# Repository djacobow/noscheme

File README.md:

# NoScheme

NoScheme is a language and compiler for designing PCB circuits using text
rather than drawing schematics.

You can write explicit components and named connections in `.nosch` files,
organize circuits into reusable blocks, and export them to KiCad for placement
and routing. It is designed as a replacement for drawing schematics in
`eeschema`: NoScheme generates the KiCad schematic, one sheet per block, and
KiCad's PCB editor updates the board from it as usual.

The aim is to make circuit descriptions easy to edit, review, and version
alongside firmware, and to provide an extensible set of static checks for
circuits that go beyond traditional ERC rules.

Arrays and reusable component definitions reduce repetition. Electrical rule
checks use declared pin roles and metadata to find connection errors, driver
conflicts, and current, pull-resistance, or capacitance budget violations.

For the time being, the NoScheme compiler and language server are written in
Python. An optional [C++23 implementation](cpp/README.md) shares its compiler
core between the CLI and LSP. Vim, Neovim, Emacs (Eglot), and the local VS Code
extension provide syntax highlighting and LSP integration for diagnostics,
definition navigation, references, rename, hover, completion, and formatting
while editing unsaved designs. `noscheme format` applies the same canonical
layout from the command line.

## History and Rationale

I started my career as a circuit designer in the semiconductor industry,
designing on-chip memories, which is a mixed analog-digital activity. For this
I used schematics, but as tools matured and more work became strictly digital,
I, along with the whole industry, moved largely towards hardware definition
languages such as iHDL (google it), VHDL, and Verilog.

Much later in my career, I found myself designing PCBs, and I was dismayed to
find that the state-of-the-art in PCBA design is still very much schematic
driven. I think this is a shame, because schematics are rather error prone and,
in particular, slow to work on, and hard to add arbitrary checks and
constraints to. Most CAD tools have ERC checks, but to get the full value of
them, you have to annotate nets and pins, which is a tonne of tedious clicking
in a GUI.

While small analog circuits are easy to understand in a visual schematic
format, such circuits comprise a smaller and smaller amount of what goes into
PCB design these days. Instead, we have complex, sprawling nests of digital
wiring and components. You can try to squeeze all those elements onto one
sheet, so you can trace wires, or you can spread them out into many sheets
using tags and named nets, but both ways are very hard for me to trace.

For more than a decade, I had the idea to make a text entry system for PCB
design. Rather than start with a general purpose HDL that supports simulation,
sophisticated generators, and other fancy features, I wanted a domain-specific
language (DSL) that is tightly bound to the target: PCBs. That's NoScheme.

I don't expect to convert many experienced PCB people to this way of working,
but I intend to use NoScheme personally for as many projects as I can manage,
and will extend it as required when I run into limitations. Because of that,
the language should be considered very much experimental, at least for the time
being.

## Status

This is an actively developed proof of concept. Several examples, including an
STM32 reference board, compile, and their netlists have successfully populated a
KiCad board. Every example's generated KiCad schematic reads back in KiCad with
the same connectivity and passes KiCad's schematic ERC. Placement, routing, and hardware validation remain separate steps.

## Documentation

- [Usage guide](USAGE.md) — install the tool, develop a circuit, check it,
  export a BOM, and carry changes into KiCad.
- [Language reference](docs/LRM.md) — normative syntax, scope, metadata, electrical rules,
  and a complete example.
- [Development](docs/DEVELOPMENT.md) — compiler development, tests, CI, and performance measurements.
- [Editor support](docs/EDITOR_SUPPORT.md) — Vim, Neovim, Emacs, and VS Code setup and LSP capabilities.
- [Project design](docs/PROJECT.md) — goals, design decisions, and reference-board details.
- [Implementation history](docs/PLAN.md) — milestone records and deferred proposals.
- [KiCad experiments](docs/experiments/README.md) and
  [findings](docs/experiments/FINDINGS.md) — manual import/update checks and results.

Runnable designs are in [examples/](examples/), including the [STM32
board](examples/stm32h523/stm32h523.nosch) and the [Rulos six-line display
matrix](examples/rulos_6matrix/README.md), transcribed from an existing
schematic using nested block and component arrays. The [WREN
examples](examples/wren/README.md) include a readable 189-component output
subsystem and a generated 1,507-component compiler/LSP benchmark. The [Honest
Millisecond Clock](examples/clock/README.md) is a new GPS-disciplined NTP clock
design with parts selected for JLCPCB assembly.

## License

NoScheme is free software, licensed under the [GNU General Public License v3.0
or later](LICENSE.md). Designs you write in NoScheme and the files it generates
from them are your own; the GPL does not apply to them.

The KiCad library snapshots under `examples/*/kicad_lib/` are derived from the
KiCad libraries and keep their CC-BY-SA 4.0 license; see the `LICENSE.md` in
each of those directories.

The [Rulos](examples/rulos_6matrix/README.md#attribution-and-sources) and
[WREN](examples/wren/README.md#attribution-and-provenance) examples also record
their upstream design attribution and source-license information.

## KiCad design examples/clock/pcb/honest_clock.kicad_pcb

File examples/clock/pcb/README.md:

# Honest Clock PCB

KiCad 10 project for the clock board. It starts empty except for the
outline, mounting holes, planes, and rules; parts arrive from the NoScheme
netlist.

## Board

- **Outline:** 226 × 64 mm, from the layout mockup. Displays face the front;
  everything else mounts on the back.
- **Stand band:** the bottom 9.525 mm (3/8 in) is a rule area named
  `stand band`. `honest_clock.kicad_dru` rejects any footprint there except
  the mounting holes, on either side.
- **Mounting holes:** five M3 holes (H1–H5): two along the top, three in the
  stand band to screw the board to its base. They are board-only footprints,
  so netlist updates keep them.
- **Origins:** the grid origin is the top-left corner; the drill/place origin
  is the bottom-left corner, for JLCPCB position files.

## Stackup

JLCPCB JLC04161H-7628: 4 layers, 1.6 mm, 1 oz outer and 0.5 oz inner copper.

| Layer | Use | Thickness |
|---|---|---|
| F.Cu | Digits (through-hole), front routing | 35 µm |
| Prepreg 7628 | εr 4.4 | 0.2104 mm |
| In1.Cu | Power: 3V3 left of x = 88 mm, 5V right | 15.2 µm |
| Core | εr 4.6 | 1.065 mm |
| In2.Cu | GND plane | 15.2 µm |
| Prepreg 7628 | εr 4.4 | 0.2104 mm |
| B.Cu | Components and most routing | 35 µm |

- **GND on In2:** the ground plane is the layer next to B.Cu, where the parts
  and fast signals are (USB, RMII, the GPS RF trace). That gives them a return
  path 0.21 mm away.
- **In1 split:** 5V feeds the LED supply, about 0.75 A spread across the
  digits on the right, so it gets the plane there. 3V3 serves the MCU, PHY,
  and GPS on the left, where most of the 3V3 pins and decoupling vias are.
  The drivers' 3V3 logic supply is a few milliamps and can run on traces.
- **Split position:** move the split once placement settles. Keep fast
  signals from crossing it on B.Cu: In2 is their reference, so that is mostly
  a concern for routing on F.Cu.

## Rules (6/6/6)

| Rule | Value |
|---|---|
| Track width, minimum | 0.1524 mm (6 mil) |
| Clearance, minimum | 0.1524 mm (6 mil) |
| Via annular ring, minimum | 0.15 mm (~6 mil) |
| Via | 0.6 mm pad on a 0.3 mm drill (also 0.8 / 0.4 preset) |
| Through-hole drill, minimum | 0.3 mm |
| Hole to hole | 0.5 mm |
| Hole to copper | 0.254 mm |
| Copper to board edge | 0.3 mm |
| Silkscreen text | 1.0 mm high, 0.15 mm stroke |

Net classes:

| Class | Track | Clearance | Via | Members |
|---|---|---|---|---|
| Default | 0.1524 mm (6 mil) | 0.1524 mm | 0.6 / 0.3 | everything else |
| Power | 0.2032 mm (8 mil) | 0.1524 mm | 0.6 / 0.3 | `vbus`, `v5`, `v3v3`, `v3v3_quiet`, `gnd` |

8 mil is a minimum for rails, not a target. Use the planes, or widen tracks
where current flows: VBUS at 12 V, the buck switch nodes and outputs, and the
LED 5 V supply.

## Project footprints

`HonestClock.pretty` holds footprints drawn for this board, registered in the
project's `fp-lib-table` as `HonestClock`:

- **`OLED_SSD1309_2.42in_Module`:** the whole 2.42" OLED module, not just its
  header: the 72 × 43 mm outline on silkscreen and courtyard, the glass and
  active area on F.Fab, the 7-pin header (origin at pin 1, GND), and four
  2.2 mm holes for M2 screws on the module's 68 × 39 mm pattern. Dimensions
  follow QDtech's MC242GX drawing; measure a real module before ordering.
- **`RJ45_HanRun_HY951180A_Vertical`:** the vertical MagJack, from HanRun's
  recommended PCB layout: eight signal pins, four LED pins, two shield tabs,
  and two 3.2 mm locating pegs. Origin at pin 1.

- **`USB_C_Receptacle_Hanxia_HX-TYPE-C-16P-180-LT-H10.0_Vertical`:** the
  vertical USB-C receptacle, from Hanxia's recommended layout: two rows of
  eight SMD pads at 1.00 mm, four SMD shell tabs, and two 0.9 mm peg holes.
  The shell tabs are 0.12 mm shorter than drawn to keep 0.25 mm from the peg
  holes.

`scripts/make_footprints.py` regenerates them from named dimensions.

After changing a footprint here, refresh its record in
`kicad_lib/footprints.json` (see [kicad_lib/README.md](../kicad_lib/README.md)).

## Scripts

`snapshots/` (local, not committed) holds a copy of the board at each
placement step, numbered in order.

Run these from KiCad's scripting console with the board open, or standalone
on a closed board (`python3 scripts/<name>.py honest_clock.kicad_pcb`):

- **`place_clusters.py`:** places the subsystems (USB/PD, bucks, GPS,
  Ethernet, timebase, MCU passives, probes) as clusters: each anchor part at
  a target spot, then its decoupling caps on its power pins and its other
  passives beside the pins or parts they connect to. Parts in `KEEP` stay
  where they were placed by hand. Edit `CLUSTERS` and rerun from a snapshot.
  With `--only REF ...` it re-places just those satellites around their
  anchors' current positions and leaves every other part where it is, which
  suits tidying up after moving parts by hand. Add `--here` to nudge named
  anchors to the nearest free spot around their current positions instead.
- **`place_display_passives.py`:** puts each digit's R-EXT below its bottom
  pin row and its driver's decoupling cap above the driver, both on the back.

## Bring parts in

From the repository root:

```sh
uv run --locked noscheme export-kicad --project examples/clock \
  --footprints examples/clock/kicad_lib/footprints.json \
  --schematic examples/clock/pcb/honest_clock.kicad_sch
```

This writes the KiCad schematic here: `honest_clock.kicad_sch` and one sheet
file per distinct block (the nine digits share `display_Digit.kicad_sch`),
plus `noscheme.kicad_sym`, registered in `sym-lib-table`. They are generated
and committed with the board; edits made in KiCad are overwritten.

1. In KiCad, open `honest_clock.kicad_pro`, then the PCB editor.
2. **Tools → Update PCB from Schematic** (F8). Review the changes, then
   **Update PCB**. The schematic editor need not be open.
3. The plane zones are already tied to `gnd`, `v3v3`, and `v5`; refill zones
   (**B**) once parts are placed.

The board was first populated from `build/board.net`, whose footprint links
differ from the schematic's. The first F8 after that needs **Re-link footprints
to schematic symbols based on their reference designators** ticked.

Net-class membership comes from `net_class: "Power"` in `main.nosch`. The
schematic carries it to the board on every update; the `Power` class's widths
and clearances stay in `honest_clock.kicad_pro`.

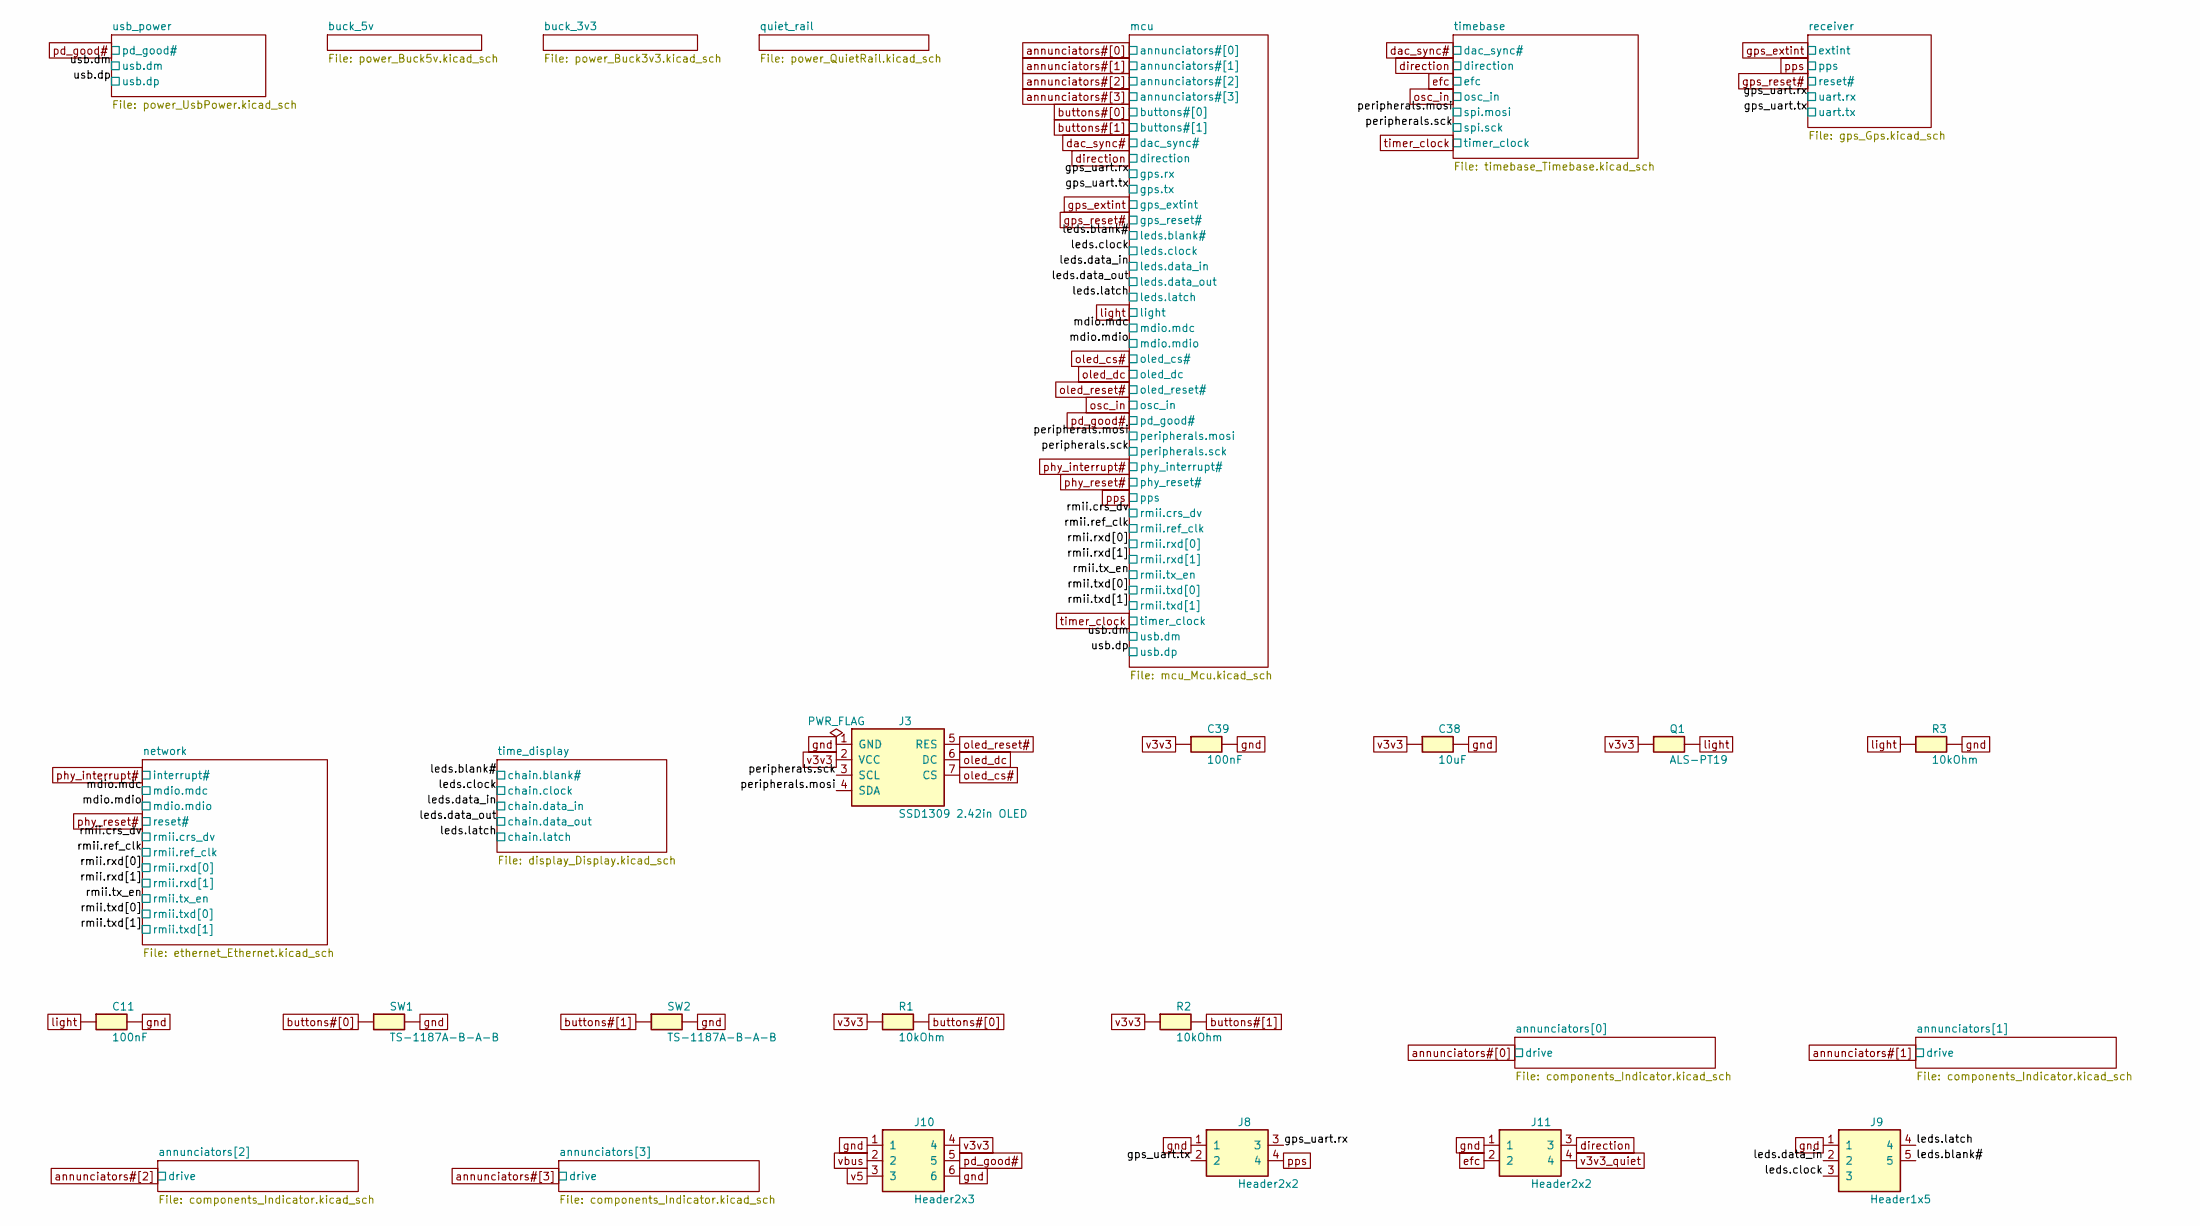
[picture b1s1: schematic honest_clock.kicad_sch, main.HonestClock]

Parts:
C11, C39: 100nF; C_0603_1608Metric
C38: 10uF; C_0805_2012Metric
J3: SSD1309 2.42in OLED; OLED_SSD1309_2.42in_Module
J8, J11: Header2x2; PinHeader_2x02_P2.54mm_Vertical_SMD
J9: Header1x5; PinHeader_1x05_P2.54mm_Vertical_SMD_Pin1Left
J10: Header2x3; PinHeader_2x03_P2.54mm_Vertical_SMD
Q1: ALS-PT19; LED_0603_1608Metric; MPN ALS-PT19-315C/L177/TR8
R1, R2, R3: 10kOhm; R_0603_1608Metric
SW1, SW2: TS-1187A-B-A-B; SW_SPST_TL3342; MPN TS-1187A-B-A-B

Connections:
/gps_uart.rx: J8.3; also elsewhere on the board
/gps_uart.tx: J8.2; also elsewhere on the board
/leds.blank#: J9.5; also elsewhere on the board
/leds.clock: J9.3; also elsewhere on the board
/leds.data_in: J9.2; also elsewhere on the board
/leds.latch: J9.4; also elsewhere on the board
/peripherals.mosi: J3.4 (SDA); also elsewhere on the board
/peripherals.sck: J3.3 (SCL); also elsewhere on the board
buttons#[0]: R1.2, SW1.1; also elsewhere on the board
buttons#[1]: R2.2, SW2.1; also elsewhere on the board
direction: J11.3; also elsewhere on the board
efc: J11.2; also elsewhere on the board
gnd: C11.2, C38.2, C39.2, J3.1 (GND), J8.1, J9.1, J10.1, J10.6, J11.1, R3.2, SW1.2, SW2.2; also elsewhere on the board
light: C11.1, Q1.2 (emitter), R3.1; also elsewhere on the board
oled_cs#: J3.7 (CS); also elsewhere on the board
oled_dc: J3.6 (DC); also elsewhere on the board
oled_reset#: J3.5 (RES); also elsewhere on the board
pd_good#: J10.5; also elsewhere on the board
pps: J8.4; also elsewhere on the board
v3v3: C38.1, C39.1, J3.2 (VCC), J10.4, Q1.1 (collector), R1.1, R2.1; also elsewhere on the board
v3v3_quiet: J11.4; also elsewhere on the board
v5: J10.3; also elsewhere on the board
vbus: J10.2; also elsewhere on the board

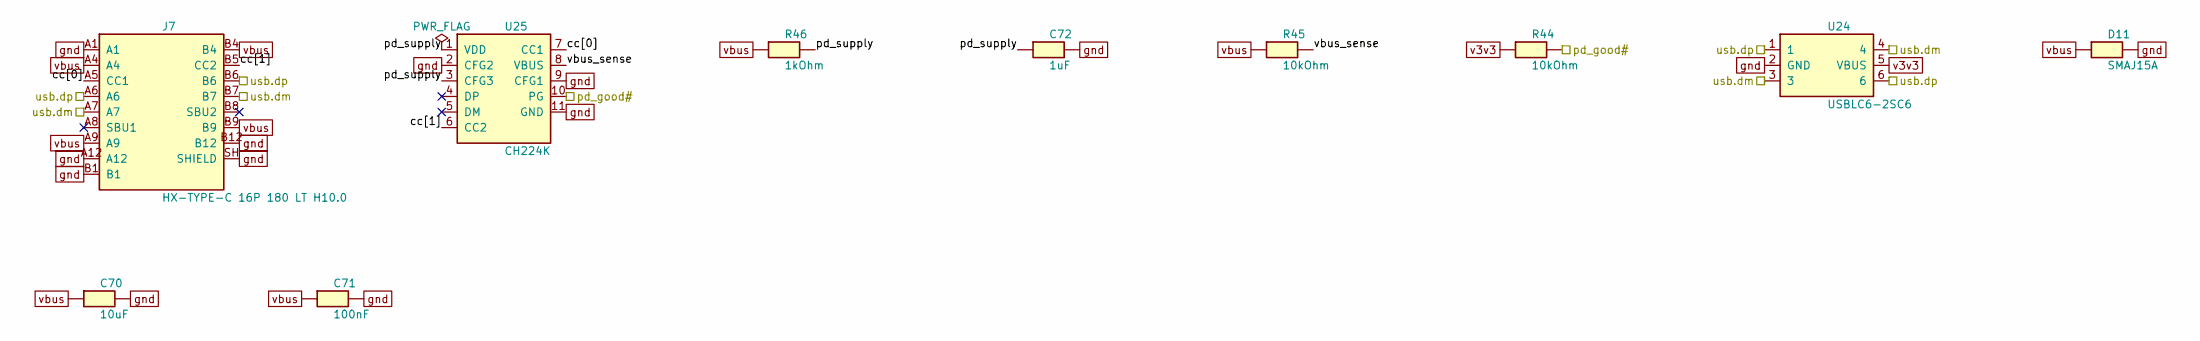
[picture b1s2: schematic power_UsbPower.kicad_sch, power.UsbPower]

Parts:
C70: 10uF; C_1206_3216Metric
C71: 100nF; C_0603_1608Metric
C72: 1uF; C_0603_1608Metric
D11: SMAJ15A; D_SMA; MPN SMAJ15A
J7: HX-TYPE-C 16P 180 LT H10.0; USB_C_Receptacle_Hanxia_HX-TYPE-C-16P-180-LT-H10.0_Vertical; MPN HX-TYPE-C 16P 180 LT H10.0
R44, R45: 10kOhm; R_0603_1608Metric
R46: 1kOhm; R_0603_1608Metric
U24: USBLC6-2SC6; SOT-23-6; MPN USBLC6-2SC6
U25: CH224K; SSOP-10-1EP_3.9x4.9mm_P1mm_EP2.1x3.3mm; MPN CH224K

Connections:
/usb.dm: J7.A7, J7.B7, U24.3, U24.4; also elsewhere on the board
/usb.dp: J7.A6, J7.B6, U24.1, U24.6; also elsewhere on the board
/usb_power/cc[0]: J7.A5 (CC1), U25.7 (CC1)
/usb_power/cc[1]: J7.B5 (CC2), U25.6 (CC2)
/usb_power/pd_supply: C72.1, R46.2, U25.1 (VDD), U25.3 (CFG3)
/usb_power/vbus_sense: R45.2, U25.8 (VBUS)
gnd: C70.2, C71.2, C72.2, D11.2 (anode), J7.A1, J7.A12, J7.B1, J7.B12, J7.SH (SHIELD), U24.2 (GND), U25.2 (CFG2), U25.9 (CFG1), U25.11 (GND); also elsewhere on the board
pd_good#: R44.2, U25.10 (PG); also elsewhere on the board
v3v3: R44.1, U24.5 (VBUS); also elsewhere on the board
vbus: C70.1, C71.1, D11.1 (cathode), J7.A4, J7.A9, J7.B4, J7.B9, R45.1, R46.1; also elsewhere on the board

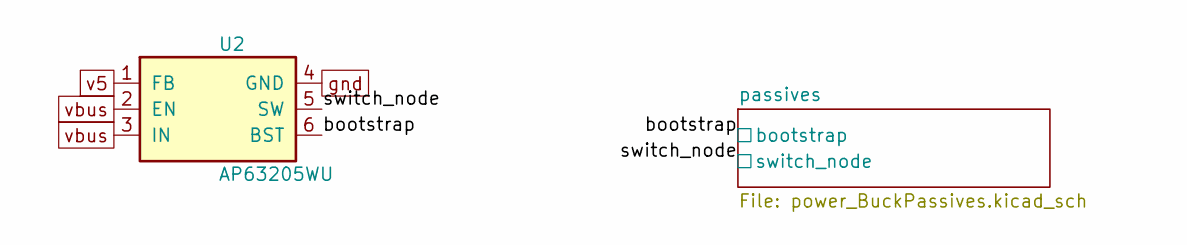
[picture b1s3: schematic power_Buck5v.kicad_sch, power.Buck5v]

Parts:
U2: AP63205WU; TSOT-23-6; MPN AP63205WU-7

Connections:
/buck_5v/bootstrap: U2.6 (BST); also elsewhere on the board
/buck_5v/switch_node: U2.5 (SW); also elsewhere on the board
gnd: U2.4 (GND); also elsewhere on the board
v5: U2.1 (FB); also elsewhere on the board
vbus: U2.2 (EN), U2.3 (IN); also elsewhere on the board

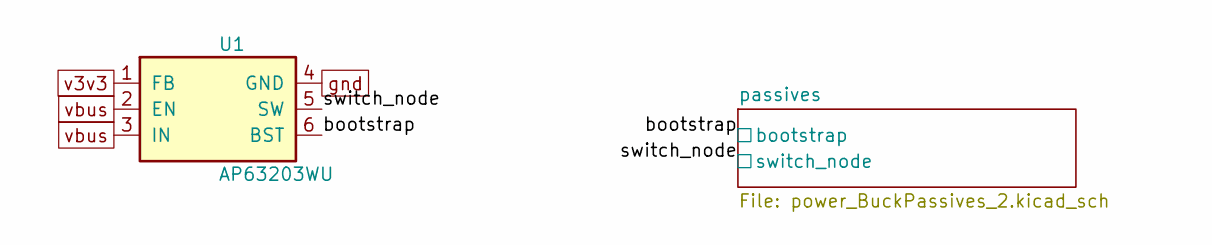
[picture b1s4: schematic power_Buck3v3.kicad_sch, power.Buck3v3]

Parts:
U1: AP63203WU; TSOT-23-6; MPN AP63203WU-7

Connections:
/buck_3v3/bootstrap: U1.6 (BST); also elsewhere on the board
/buck_3v3/switch_node: U1.5 (SW); also elsewhere on the board
gnd: U1.4 (GND); also elsewhere on the board
v3v3: U1.1 (FB); also elsewhere on the board
vbus: U1.2 (EN), U1.3 (IN); also elsewhere on the board

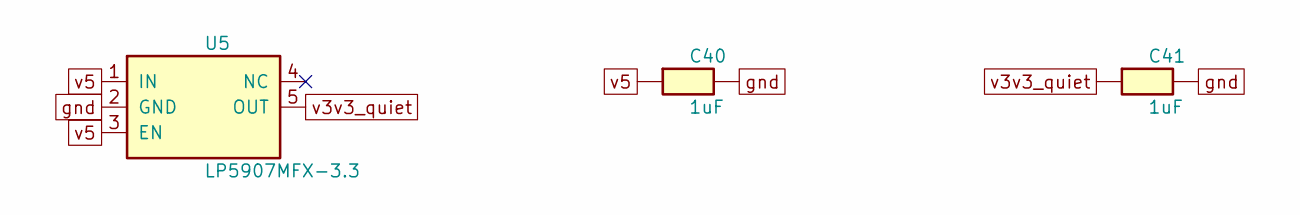
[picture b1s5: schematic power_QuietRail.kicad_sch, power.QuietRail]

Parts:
C40, C41: 1uF; C_0603_1608Metric
U5: LP5907MFX-3.3; SOT-23-5; MPN LP5907MFX-3.3/NOPB

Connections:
gnd: C40.2, C41.2, U5.2 (GND); also elsewhere on the board
v3v3_quiet: C41.1, U5.5 (OUT); also elsewhere on the board
v5: C40.1, U5.1 (IN), U5.3 (EN); also elsewhere on the board

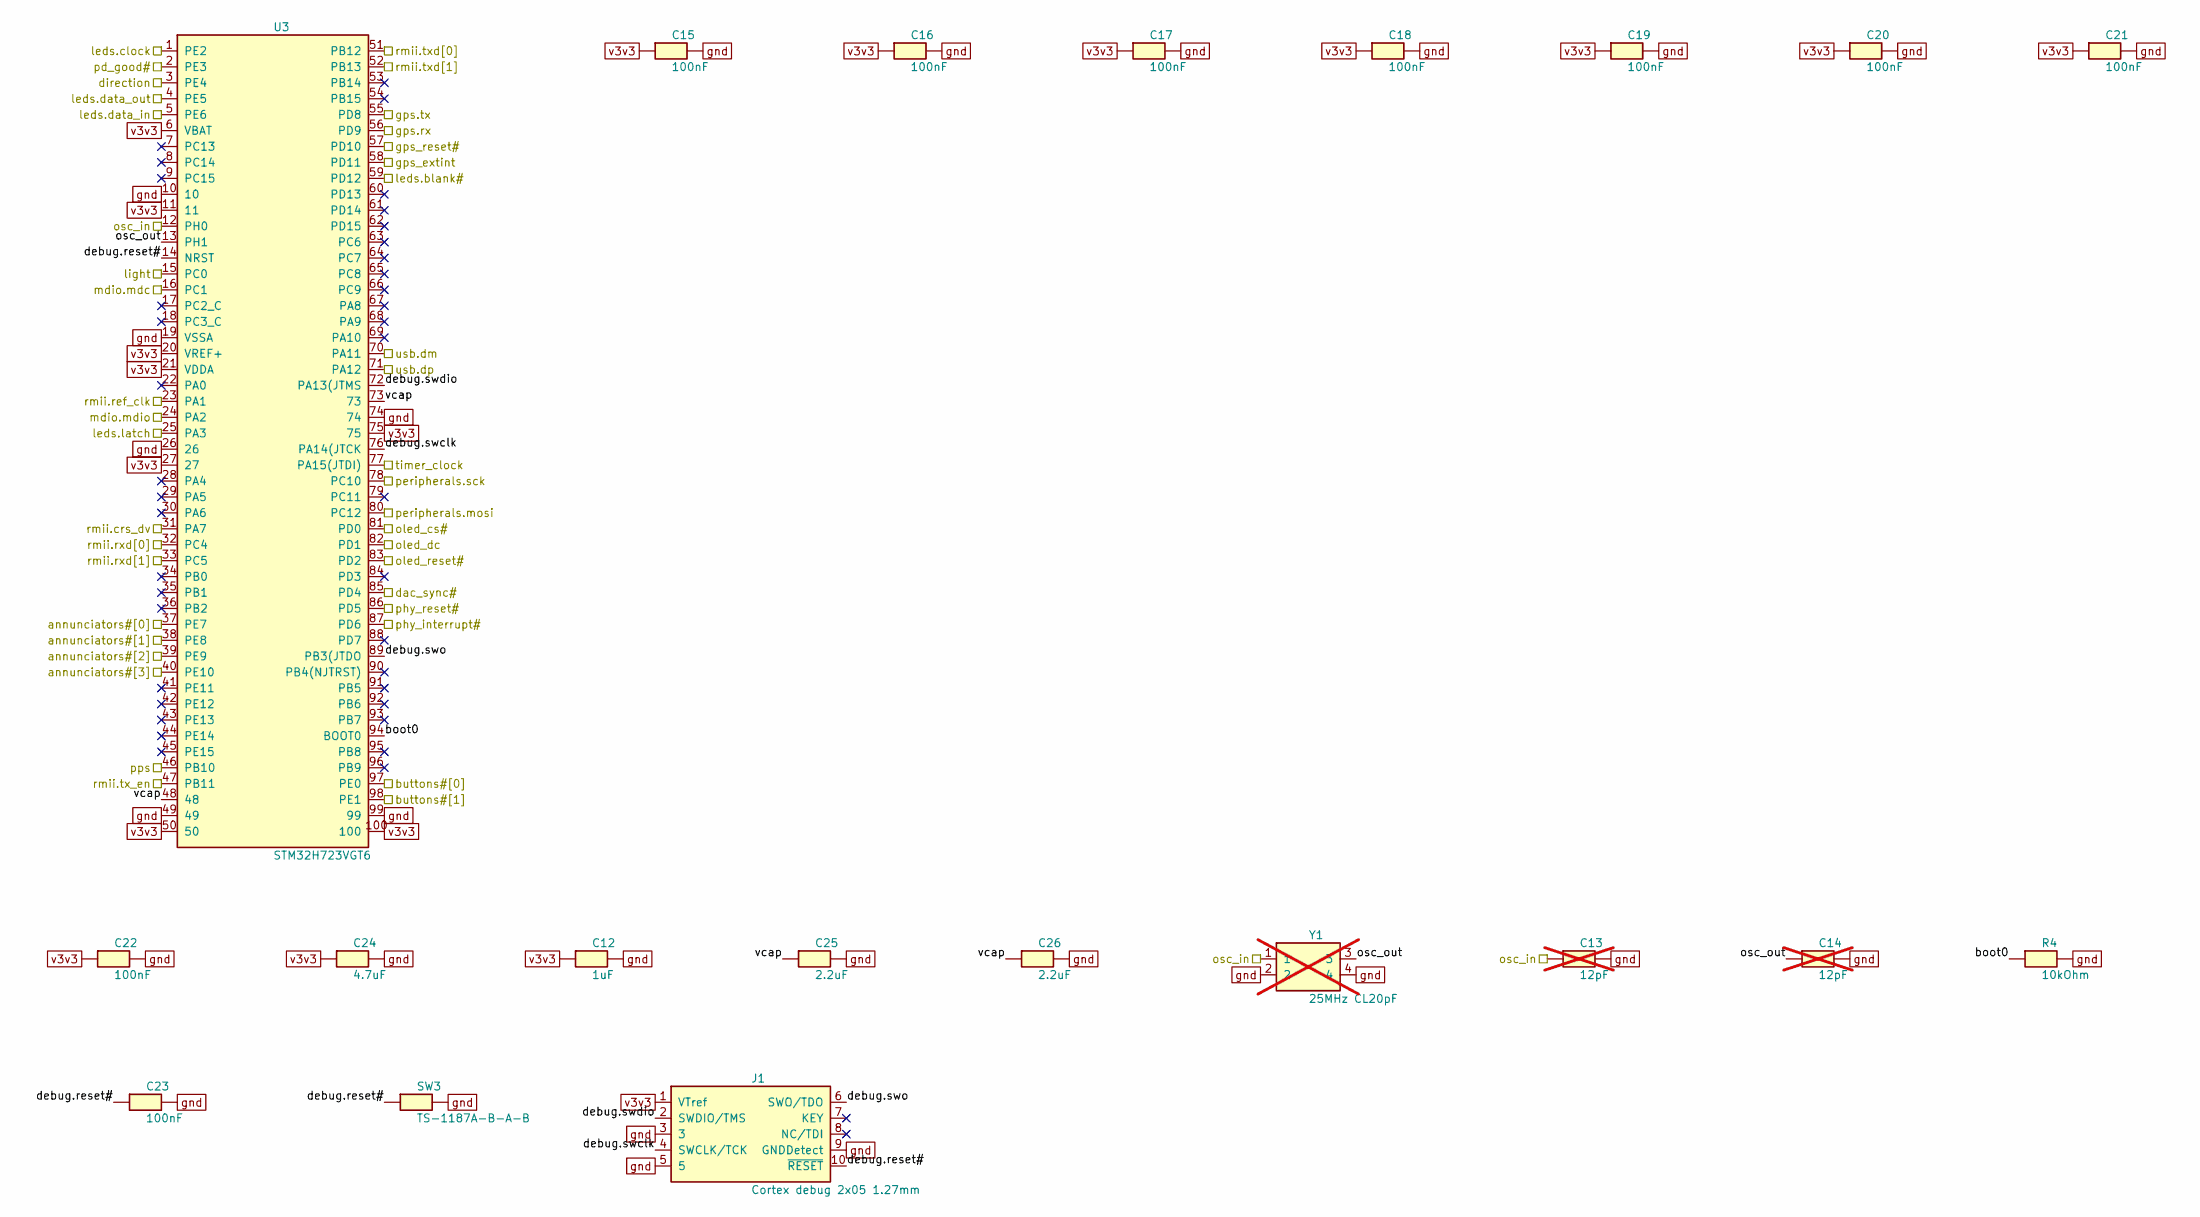
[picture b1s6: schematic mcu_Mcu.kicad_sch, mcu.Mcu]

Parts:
C12: 1uF; C_0603_1608Metric
C13, C14: 12pF; C_0603_1608Metric; not fitted
C15, C16, C17, C18, C19, C20, C21, C22, C23: 100nF; C_0603_1608Metric
C24: 4.7uF; C_0603_1608Metric
C25, C26: 2.2uF; C_0603_1608Metric
J1: Cortex debug 2x05 1.27mm; PinHeader_2x05_P1.27mm_Vertical_SMD
R4: 10kOhm; R_0603_1608Metric
SW3: TS-1187A-B-A-B; SW_SPST_TL3342; MPN TS-1187A-B-A-B
U3: STM32H723VGT6; LQFP-100_14x14mm_P0.5mm; MPN STM32H723VGT6
Y1: 25MHz CL20pF; Crystal_SMD_3225-4Pin_3.2x2.5mm; MPN X322525MOB4SI; not fitted

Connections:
/gps_uart.rx: U3.56 (PD9); also elsewhere on the board
/gps_uart.tx: U3.55 (PD8); also elsewhere on the board
/leds.blank#: U3.59 (PD12); also elsewhere on the board
/leds.clock: U3.1 (PE2); also elsewhere on the board
/leds.data_in: U3.5 (PE6); also elsewhere on the board
/leds.data_out: U3.4 (PE5); also elsewhere on the board
/leds.latch: U3.25 (PA3); also elsewhere on the board
/mcu/boot0: R4.1, U3.94 (BOOT0)
/mcu/debug.reset#: C23.1, J1.10 (~RESET), SW3.1, U3.14 (NRST)
/mcu/debug.swclk: J1.4 (SWCLK/TCK), U3.76 (PA14(JTCK)
/mcu/debug.swdio: J1.2 (SWDIO/TMS), U3.72 (PA13(JTMS)
/mcu/debug.swo: J1.6 (SWO/TDO), U3.89 (PB3(JTDO)
/mcu/osc_out: C14.1, U3.13 (PH1), Y1.3
/mcu/vcap: C25.1, C26.1, U3.48, U3.73
/mdio.mdc: U3.16 (PC1); also elsewhere on the board
/mdio.mdio: U3.24 (PA2); also elsewhere on the board
/peripherals.mosi: U3.80 (PC12); also elsewhere on the board
/peripherals.sck: U3.78 (PC10); also elsewhere on the board
/rmii.crs_dv: U3.31 (PA7); also elsewhere on the board
/rmii.ref_clk: U3.23 (PA1); also elsewhere on the board
/rmii.rxd[0]: U3.32 (PC4); also elsewhere on the board
/rmii.rxd[1]: U3.33 (PC5); also elsewhere on the board
/rmii.tx_en: U3.47 (PB11); also elsewhere on the board
/rmii.txd[0]: U3.51 (PB12); also elsewhere on the board
/rmii.txd[1]: U3.52 (PB13); also elsewhere on the board
/usb.dm: U3.70 (PA11); also elsewhere on the board
/usb.dp: U3.71 (PA12); also elsewhere on the board
annunciators#[0]: U3.37 (PE7); also elsewhere on the board
annunciators#[1]: U3.38 (PE8); also elsewhere on the board
annunciators#[2]: U3.39 (PE9); also elsewhere on the board
annunciators#[3]: U3.40 (PE10); also elsewhere on the board
buttons#[0]: U3.97 (PE0); also elsewhere on the board
buttons#[1]: U3.98 (PE1); also elsewhere on the board
dac_sync#: U3.85 (PD4); also elsewhere on the board
direction: U3.3 (PE4); also elsewhere on the board
gnd: C12.2, C13.2, C14.2, C15.2, C16.2, C17.2, C18.2, C19.2, C20.2, C21.2, C22.2, C23.2, C24.2, C25.2, C26.2, J1.3, J1.5, J1.9 (GNDDetect), R4.2, SW3.2, U3.10, U3.19 (VSSA), U3.26, U3.49, U3.74, U3.99, Y1.2, Y1.4; also elsewhere on the board
gps_extint: U3.58 (PD11); also elsewhere on the board
gps_reset#: U3.57 (PD10); also elsewhere on the board
light: U3.15 (PC0); also elsewhere on the board
oled_cs#: U3.81 (PD0); also elsewhere on the board
oled_dc: U3.82 (PD1); also elsewhere on the board
oled_reset#: U3.83 (PD2); also elsewhere on the board
osc_in: C13.1, U3.12 (PH0), Y1.1; also elsewhere on the board
pd_good#: U3.2 (PE3); also elsewhere on the board
phy_interrupt#: U3.87 (PD6); also elsewhere on the board
phy_reset#: U3.86 (PD5); also elsewhere on the board
pps: U3.46 (PB10); also elsewhere on the board
timer_clock: U3.77 (PA15(JTDI)); also elsewhere on the board
v3v3: C12.1, C15.1, C16.1, C17.1, C18.1, C19.1, C20.1, C21.1, C22.1, C24.1, J1.1 (VTref), U3.6 (VBAT), U3.11, U3.20 (VREF+), U3.21 (VDDA), U3.27, U3.50, U3.75, U3.100; also elsewhere on the board

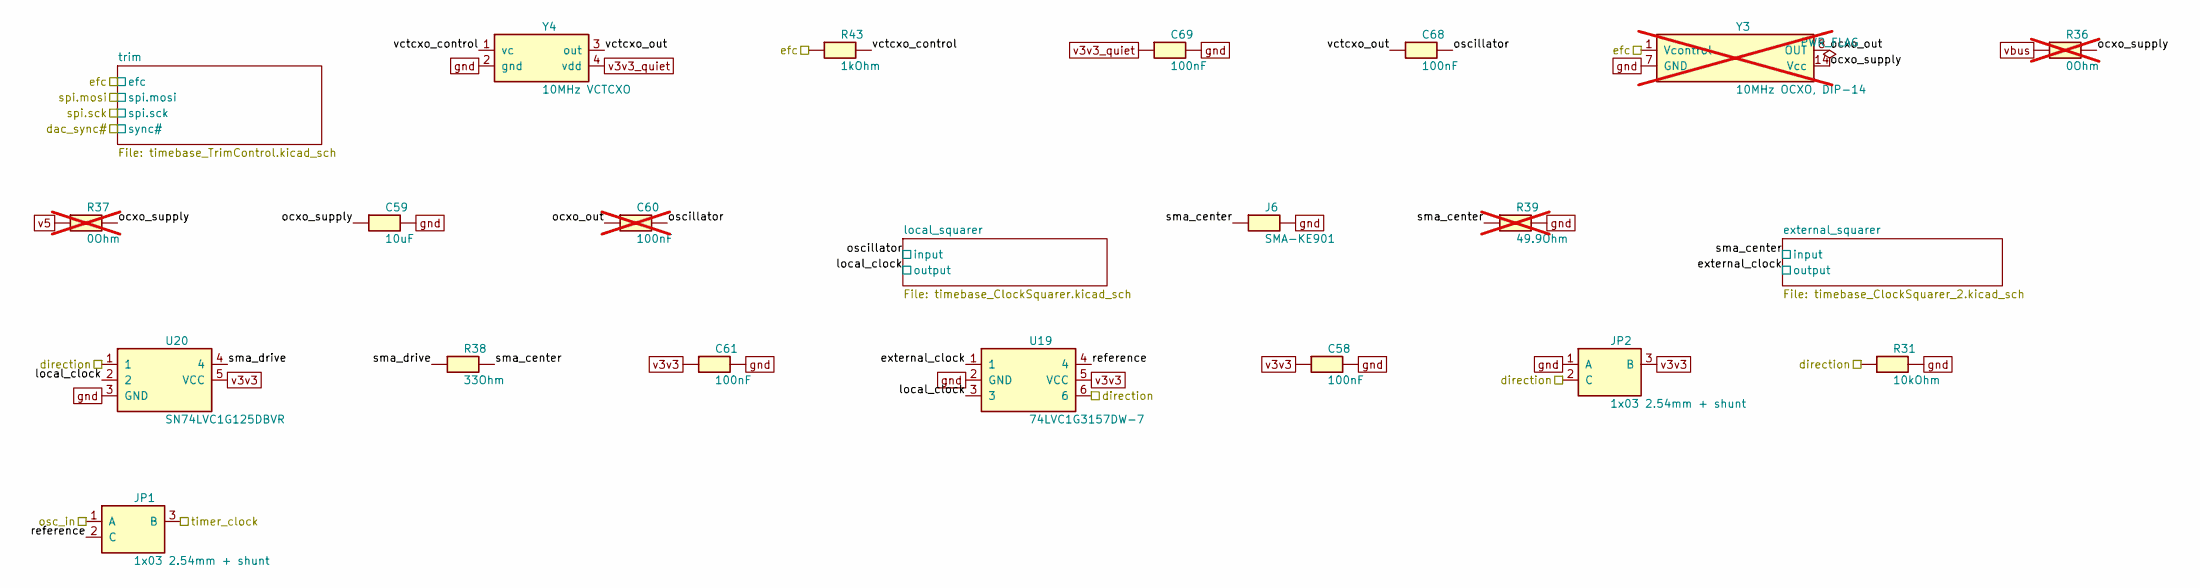
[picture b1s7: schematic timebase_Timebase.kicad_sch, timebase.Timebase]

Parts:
C58, C61, C68, C69: 100nF; C_0603_1608Metric
C59: 10uF; C_0805_2012Metric
C60: 100nF; C_0603_1608Metric; not fitted
J6: SMA-KE901; SMA_Amphenol_132134_Vertical; MPN SMA-KE901
JP1, JP2: 1x03 2.54mm + shunt; PinHeader_1x03_P2.54mm_Vertical_SMD_Pin1Left
R31: 10kOhm; R_0603_1608Metric
R36, R37: 0Ohm; R_0603_1608Metric; not fitted
R38: 33Ohm; R_0603_1608Metric
R39: 49.9Ohm; R_0603_1608Metric; not fitted
R43: 1kOhm; R_0603_1608Metric
U19: 74LVC1G3157DW-7; SOT-363_SC-70-6; MPN 74LVC1G3157DW-7
U20: SN74LVC1G125DBVR; SOT-23-5; MPN SN74LVC1G125DBVR
Y3: 10MHz OCXO, DIP-14; Oscillator_DIP-14; not fitted
Y4: 10MHz VCTCXO; Oscillator_SMD_Abracon_ASE-4Pin_3.2x2.5mm; MPN ECS-VC-TXO32-S3-33-100-BN-TR

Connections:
/timebase/external_clock: U19.1; also elsewhere on the board
/timebase/local_clock: U19.3, U20.2; also elsewhere on the board
/timebase/ocxo_out: C60.1, Y3.8 (OUT)
/timebase/ocxo_supply: C59.1, R36.2, R37.2, Y3.14 (Vcc)
/timebase/oscillator: C60.2, C68.2; also elsewhere on the board
/timebase/reference: JP1.2 (C), U19.4
/timebase/sma_center: J6.1 (In), R38.2, R39.1; also elsewhere on the board
/timebase/sma_drive: R38.1, U20.4
/timebase/vctcxo_control: R43.2, Y4.1 (vc)
/timebase/vctcxo_out: C68.1, Y4.3 (out)
direction: JP2.2 (C), R31.1, U19.6, U20.1; also elsewhere on the board
efc: R43.1, Y3.1 (Vcontrol); also elsewhere on the board
gnd: C58.2, C59.2, C61.2, C69.2, J6.2 (Ext), JP2.1 (A), R31.2, R39.2, U19.2 (GND), U20.3 (GND), Y3.7 (GND), Y4.2 (gnd); also elsewhere on the board
osc_in: JP1.1 (A); also elsewhere on the board
timer_clock: JP1.3 (B); also elsewhere on the board
v3v3: C58.1, C61.1, JP2.3 (B), U19.5 (VCC), U20.5 (VCC); also elsewhere on the board
v3v3_quiet: C69.1, Y4.4 (vdd); also elsewhere on the board
v5: R37.1; also elsewhere on the board
vbus: R36.1; also elsewhere on the board

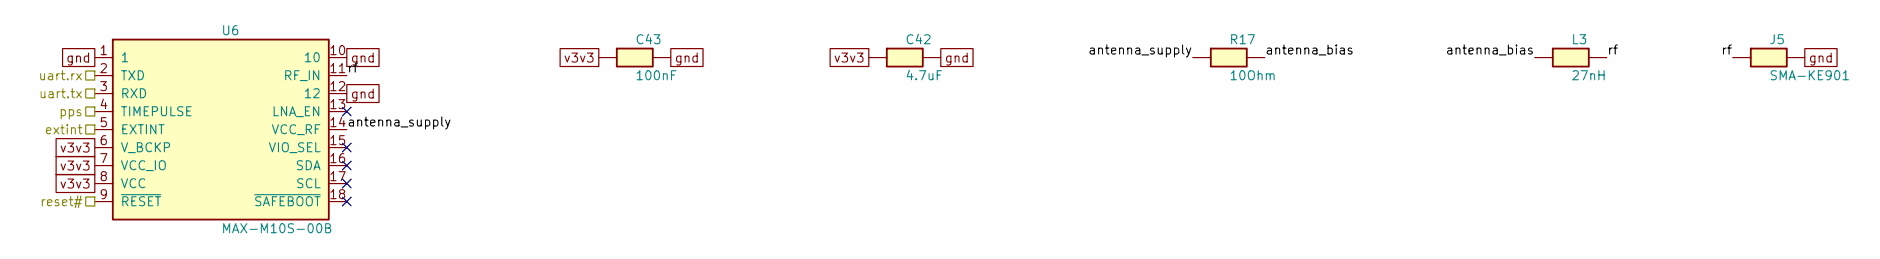
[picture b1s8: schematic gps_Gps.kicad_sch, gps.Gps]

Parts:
C42: 4.7uF; C_0603_1608Metric
C43: 100nF; C_0603_1608Metric
J5: SMA-KE901; SMA_Amphenol_132134_Vertical; MPN SMA-KE901
L3: 27nH; L_0603_1608Metric
R17: 10Ohm; R_0603_1608Metric
U6: MAX-M10S-00B; ublox_MAX; MPN MAX-M10S-00B

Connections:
/gps_uart.rx: U6.2 (TXD); also elsewhere on the board
/gps_uart.tx: U6.3 (RXD); also elsewhere on the board
/receiver/antenna_bias: L3.1, R17.2
/receiver/antenna_supply: R17.1, U6.14 (VCC_RF)
/receiver/rf: J5.1 (In), L3.2, U6.11 (RF_IN)
gnd: C42.2, C43.2, J5.2 (Ext), U6.1, U6.10, U6.12; also elsewhere on the board
gps_extint: U6.5 (EXTINT); also elsewhere on the board
gps_reset#: U6.9 (~RESET); also elsewhere on the board
pps: U6.4 (TIMEPULSE); also elsewhere on the board
v3v3: C42.1, C43.1, U6.6 (V_BCKP), U6.7 (VCC_IO), U6.8 (VCC); also elsewhere on the board

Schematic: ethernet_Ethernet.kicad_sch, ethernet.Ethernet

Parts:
C27, C28, C30, C31, C32, C33, C35, C36, C37: 100nF; C_0603_1608Metric
C29, C34: 10uF; C_0805_2012Metric
J2: HY951180A; RJ45_HanRun_HY951180A_Vertical; MPN HY951180A
R5: 4.87kOhm; R_0603_1608Metric
R6, R16: 330Ohm; R_0603_1608Metric
R7: 10kOhm; R_0603_1608Metric
R8, R9, R10, R11: 49.9Ohm; R_0603_1608Metric
R12: 1.5kOhm; R_0603_1608Metric
R13, R14, R15: 2.2kOhm; R_0603_1608Metric
U4: DP83848CVVX/NOPB; LQFP-48_7x7mm_P0.5mm; MPN DP83848CVVX/NOPB
Y2: 50MHz; Oscillator_SMD_Abracon_ASE-4Pin_3.2x2.5mm; MPN O9322550MEDA4SI

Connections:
/mdio.mdc: U4.31 (MDC); also elsewhere on the board
/mdio.mdio: R12.2, U4.30 (MDIO); also elsewhere on the board
/network/activity_led: J2.11 (YELLOW_K), U4.26
/network/green_anode: J2.9 (GREEN_A), R6.2
/network/line[0]: J2.1 (TD+), R8.2, U4.17 (TD_P)
/network/line[1]: J2.2 (TD-), R9.2, U4.16 (TD_N)
/network/line[2]: J2.6 (RD+), R10.2, U4.14 (RD_P)
/network/line[3]: J2.7 (RD-), R11.2, U4.13 (RD_N)
/network/link_led: J2.10 (GREEN_K), U4.28
/network/mii_mode: R15.2, U4.39 (MII_MODE)
/network/rbias: R5.1, U4.24 (RBIAS)
/network/regulator_feedback: C29.1, C30.1, C31.1, C32.1, U4.18, U4.23 (PFBOUT), U4.37
/network/reserved[0]: R13.2, U4.20
/network/reserved[1]: R14.2, U4.21
/network/yellow_anode: J2.12 (YELLOW_A), R16.2
/rmii.crs_dv: U4.40 (CRS_DV); also elsewhere on the board
/rmii.ref_clk: U4.34 (X1), Y2.3 (out); also elsewhere on the board
/rmii.rxd[0]: U4.43 (RXD_0); also elsewhere on the board
/rmii.rxd[1]: U4.44 (RXD_1); also elsewhere on the board
/rmii.tx_en: U4.2 (TX_EN); also elsewhere on the board
/rmii.txd[0]: U4.3 (TXD_0); also elsewhere on the board
/rmii.txd[1]: U4.4 (TXD_1); also elsewhere on the board
gnd: C27.2, C28.2, C29.2, C30.2, C31.2, C32.2, C33.2, C34.2, C35.2, C36.2, C37.2, J2.8 (CHS_GND), J2.SH, R5.2, U4.5 (TXD_2), U4.6 (TXD_3), U4.15, U4.19, U4.35, U4.36, U4.47, Y2.2 (gnd); also elsewhere on the board
phy_interrupt#: R7.2, U4.7 (PWR_DOWN_INT); also elsewhere on the board
phy_reset#: U4.29 (RESET_N); also elsewhere on the board
v3v3: C27.1, C28.1, C33.1, C34.1, C35.1, C36.1, C37.1, J2.3 (TCT), J2.5 (RCT), R6.1, R7.1, R8.1, R9.1, R10.1, R11.1, R12.1, R13.1, R14.1, R15.1, R16.1, U4.22, U4.32, U4.48, Y2.1 (oe), Y2.4 (vdd); also elsewhere on the board

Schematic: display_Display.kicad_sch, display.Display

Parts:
R20: 10kOhm; R_0603_1608Metric

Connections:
/leds.blank#: R20.2; also elsewhere on the board
v3v3: R20.1; also elsewhere on the board

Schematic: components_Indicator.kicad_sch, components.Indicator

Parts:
D12: Green; LED_0603_1608Metric
R56: 330Ohm; R_0603_1608Metric

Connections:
/annunciators[0]/cathode: D12.1 (K), R56.2
annunciators#[0]: R56.1; also elsewhere on the board
v3v3: D12.2 (A); also elsewhere on the board

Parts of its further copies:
D13, D14, D15: Green; LED_0603_1608Metric
R57, R58, R59: 330Ohm; R_0603_1608Metric

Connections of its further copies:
/annunciators[1]/cathode: D13.1 (K), R57.2
/annunciators[2]/cathode: D14.1 (K), R58.2
/annunciators[3]/cathode: D15.1 (K), R59.2
annunciators#[1]: R57.1; also elsewhere on the board
annunciators#[2]: R58.1; also elsewhere on the board
annunciators#[3]: R59.1; also elsewhere on the board
v3v3: D13.2 (A), D14.2 (A), D15.2 (A); also elsewhere on the board

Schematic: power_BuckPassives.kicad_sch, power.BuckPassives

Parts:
C6, C8: 100nF; C_0603_1608Metric
C7: 10uF; C_1206_3216Metric
C9, C10: 22uF; C_0805_2012Metric
L2: 4.7uH; L_Taiyo-Yuden_NR-50xx

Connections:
/buck_5v/bootstrap: C6.1; also elsewhere on the board
/buck_5v/switch_node: C6.2, L2.1; also elsewhere on the board
gnd: C7.2, C8.2, C9.2, C10.2; also elsewhere on the board
v5: C9.1, C10.1, L2.2; also elsewhere on the board
vbus: C7.1, C8.1; also elsewhere on the board

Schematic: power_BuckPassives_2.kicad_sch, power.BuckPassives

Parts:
C1, C3: 100nF; C_0603_1608Metric
C2: 10uF; C_1206_3216Metric
C4, C5: 22uF; C_0805_2012Metric
L1: 3.3uH; L_Taiyo-Yuden_NR-50xx

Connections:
/buck_3v3/bootstrap: C1.1; also elsewhere on the board
/buck_3v3/switch_node: C1.2, L1.1; also elsewhere on the board
gnd: C2.2, C3.2, C4.2, C5.2; also elsewhere on the board
v3v3: C4.1, C5.1, L1.2; also elsewhere on the board
vbus: C2.1, C3.1; also elsewhere on the board

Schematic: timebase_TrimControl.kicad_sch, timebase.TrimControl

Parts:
C62, C64: 100nF; C_0603_1608Metric
C63, C66, C67: 1uF; C_0603_1608Metric
C65: 10uF; C_0805_2012Metric
R40, R42: 10kOhm; R_0603_1608Metric
R41: 5.6kOhm; R_0603_1608Metric
U21: MCP6001T-I/OT; SOT-23-5; MPN MCP6001T-I/OT
U22: DAC8551IDGKR; VSSOP-8_3x3mm_P0.65mm; MPN DAC8551IDGKR
U23: REF3025AIDBZR; SOT-23; MPN REF3025AIDBZR

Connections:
/peripherals.mosi: U22.7 (D_{IN}); also elsewhere on the board
/peripherals.sck: U22.6 (SCLK); also elsewhere on the board
/timebase/trim/dac_out: R40.1, U22.3 (V_{FB}), U22.4 (V_{OUT})
/timebase/trim/feedback: R41.2, R42.1, U21.4 (-)
/timebase/trim/filtered: C65.1, R40.2, U21.3 (+)
/timebase/trim/reference: C67.1, U22.2 (V_{REF}), U23.2 (OUT)
dac_sync#: U22.5 (~SYNC); also elsewhere on the board
efc: R41.1, U21.1; also elsewhere on the board
gnd: C62.2, C63.2, C64.2, C65.2, C66.2, C67.2, R42.2, U21.2 (V-), U22.8 (GND), U23.3 (GND); also elsewhere on the board
v3v3_quiet: C63.1, C64.1, C66.1, U22.1 (V_{DD}), U23.1 (IN); also elsewhere on the board
v5: C62.1, U21.5 (V+); also elsewhere on the board

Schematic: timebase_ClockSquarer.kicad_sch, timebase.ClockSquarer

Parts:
C56, C57: 100nF; C_0603_1608Metric
R34, R35: 10kOhm; R_0603_1608Metric
U18: 74LVC1G17GV; SOT-23-5; MPN 74LVC1G17GV,125

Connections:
/timebase/local_clock: U18.4; also elsewhere on the board
/timebase/local_squarer/biased: C56.2, R34.2, R35.1, U18.2
/timebase/oscillator: C56.1; also elsewhere on the board
gnd: C57.2, R35.2, U18.3 (GND); also elsewhere on the board
v3v3_quiet: C57.1, R34.1, U18.5 (VCC); also elsewhere on the board

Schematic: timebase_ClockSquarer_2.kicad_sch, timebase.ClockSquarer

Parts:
C54, C55: 100nF; C_0603_1608Metric
R32, R33: 10kOhm; R_0603_1608Metric
U17: 74LVC1G17GV; SOT-23-5; MPN 74LVC1G17GV,125

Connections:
/timebase/external_clock: U17.4; also elsewhere on the board
/timebase/external_squarer/biased: C54.2, R32.2, R33.1, U17.2
/timebase/sma_center: C54.1; also elsewhere on the board
gnd: C55.2, R33.2, U17.3 (GND); also elsewhere on the board
v3v3: C55.1, R32.1, U17.5 (VCC); also elsewhere on the board
